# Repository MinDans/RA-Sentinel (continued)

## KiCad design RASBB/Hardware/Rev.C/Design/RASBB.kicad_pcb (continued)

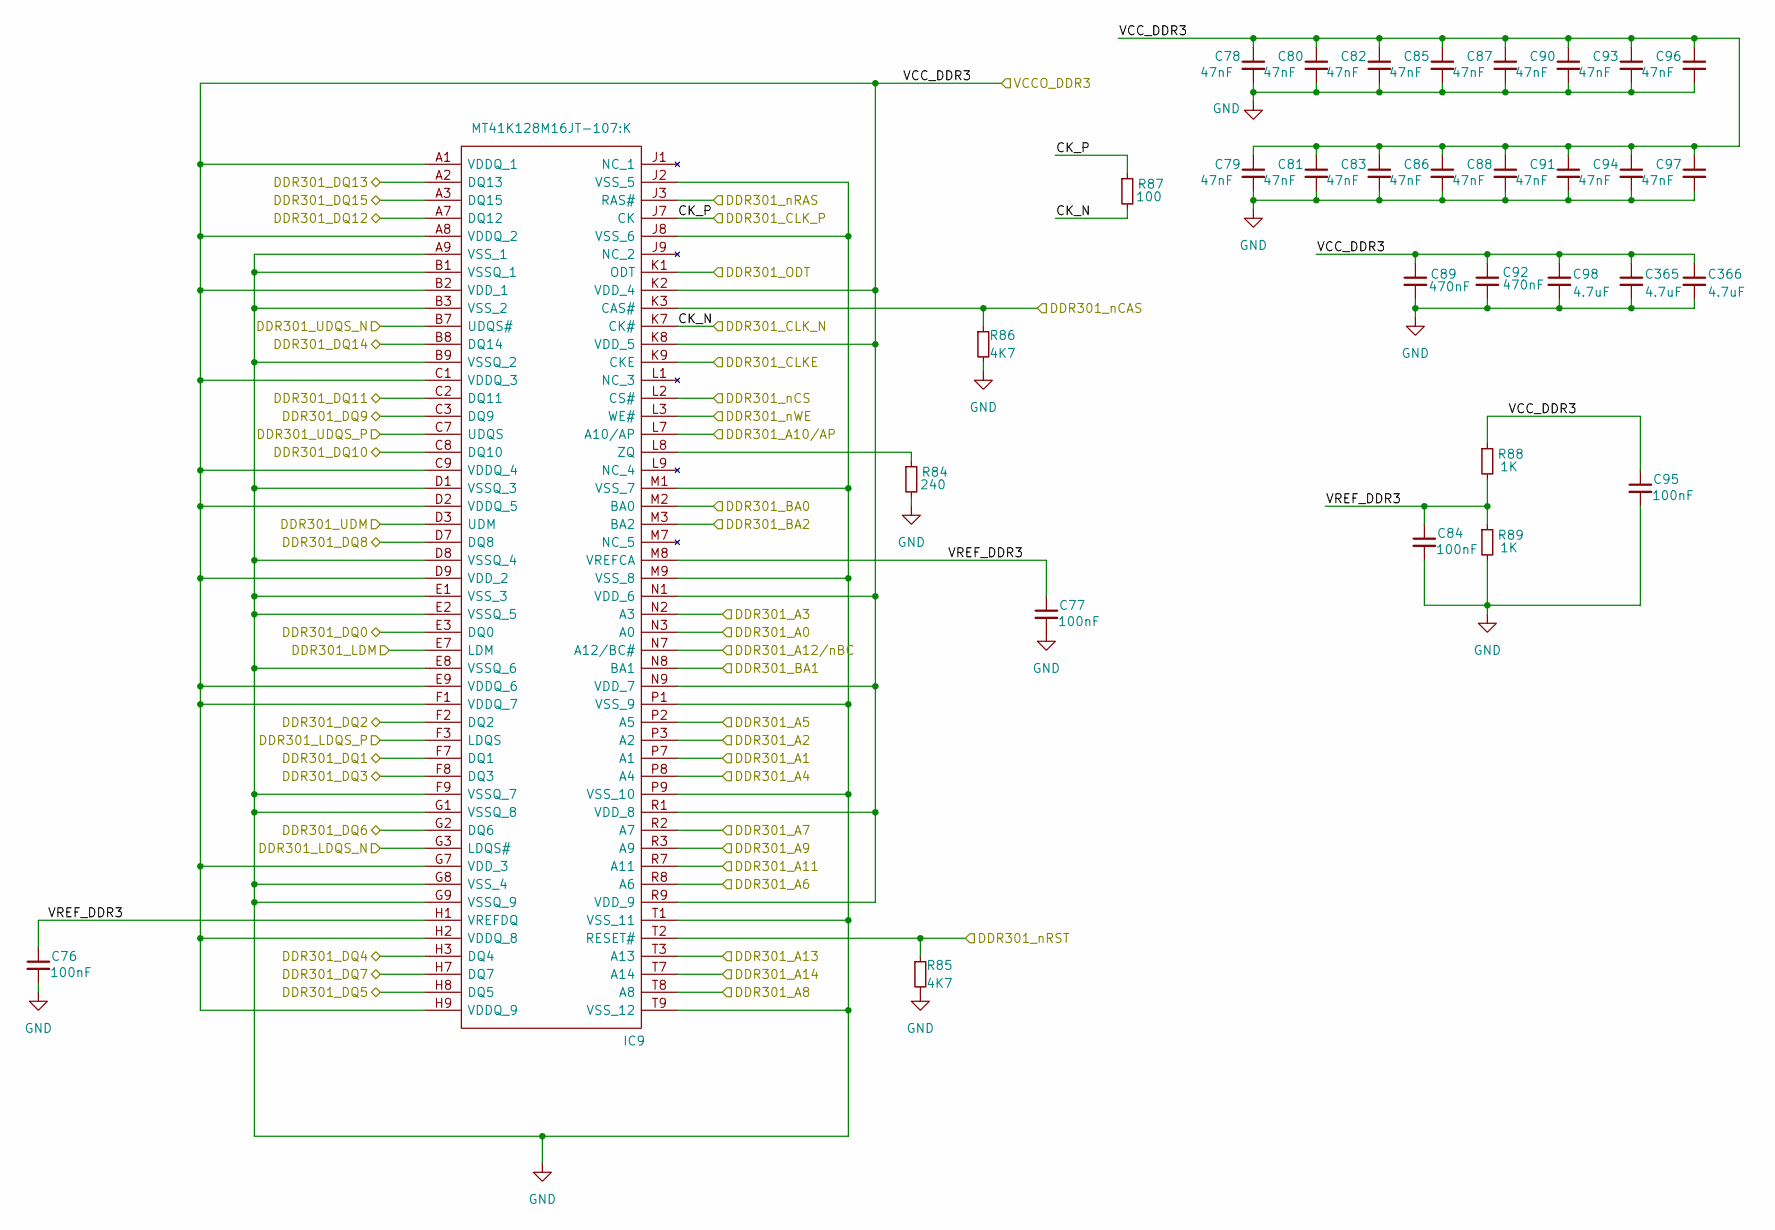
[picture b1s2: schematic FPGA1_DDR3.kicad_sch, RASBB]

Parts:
C76, C77, C84, C95: 100nF; C_0402_1005Metric; Mfr. Part # 0402B104K500CT; LCSC Part # C152814
C78, C79, C80, C81, C82, C83, C85, C86, C87, C88, C90, C91, C93, C94, C96, C97: 47nF; C_0402_1005Metric; Mfr. Part # C0402C473J8RAC7867; LCSC Part # C2178375
C89, C92: 470nF; C_0402_1005Metric; Mfr. Part # GRT155R71A474KE01D; LCSC Part # C471404
C98, C365, C366: 4.7uF; C_0603_1608Metric; Mfr. Part # GMK107BBJ475KA-T; LCSC Part # C7281848
IC9: MT41K128M16JT-107:K; BGA96C80P9X16_800X1400X120; Mfr. Part # MT41K128M16JT-107:K; LCSC Part # C2841151
R84: 240; R_0402_1005Metric; Mfr. Part # RT0402BRE07240RL; LCSC Part # C728568
R85, R86: 4K7; R_0402_1005Metric; Mfr. Part # RC0402FR-074K7L; LCSC Part # C105871
R87: 100; R_0402_1005Metric; Mfr. Part # WR04X1000FTL; LCSC Part # C163808
R88, R89: 1K; R_0402_1005Metric; Mfr. Part # MR04X1001FTL; LCSC Part # C327796

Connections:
+1V35: C78.1, C79.1, C80.1, C81.1, C82.1, C83.1, C85.1, C86.1, C87.1, C88.1, C89.1, C90.1, C91.1, C92.1, C93.1, C94.1, C95.1, C96.1, C97.1, C98.1, C365.1, C366.1, IC9.A1 (VDDQ_1), IC9.A8 (VDDQ_2), IC9.B2 (VDD_1), IC9.C1 (VDDQ_3), IC9.C9 (VDDQ_4), IC9.D2 (VDDQ_5), IC9.D9 (VDD_2), IC9.E9 (VDDQ_6), IC9.F1 (VDDQ_7), IC9.G7 (VDD_3), IC9.H2 (VDDQ_8), IC9.H9 (VDDQ_9), IC9.K2 (VDD_4), IC9.K8 (VDD_5), IC9.N1 (VDD_6), IC9.N9 (VDD_7), IC9.R1 (VDD_8), IC9.R9 (VDD_9), R88.1; also elsewhere on the board
/DDR3-01/CK_N: IC9.K7 (CK#), R87.2; also elsewhere on the board
/DDR3-01/CK_P: IC9.J7 (CK), R87.1; also elsewhere on the board
/DDR3-01/DDR301_A0: IC9.N3 (A0); also elsewhere on the board
/DDR3-01/DDR301_A1: IC9.P7 (A1); also elsewhere on the board
/DDR3-01/DDR301_A2: IC9.P3 (A2); also elsewhere on the board
/DDR3-01/DDR301_A3: IC9.N2 (A3); also elsewhere on the board
/DDR3-01/DDR301_A4: IC9.P8 (A4); also elsewhere on the board
/DDR3-01/DDR301_A5: IC9.P2 (A5); also elsewhere on the board
/DDR3-01/DDR301_A6: IC9.R8 (A6); also elsewhere on the board
/DDR3-01/DDR301_A7: IC9.R2 (A7); also elsewhere on the board
/DDR3-01/DDR301_A8: IC9.T8 (A8); also elsewhere on the board
/DDR3-01/DDR301_A9: IC9.R3 (A9); also elsewhere on the board
/DDR3-01/DDR301_A10/AP: IC9.L7 (A10/AP); also elsewhere on the board
/DDR3-01/DDR301_A11: IC9.R7 (A11); also elsewhere on the board
/DDR3-01/DDR301_A12/nBC: IC9.N7 (A12/BC#); also elsewhere on the board
/DDR3-01/DDR301_A13: IC9.T3 (A13); also elsewhere on the board
/DDR3-01/DDR301_A14: IC9.T7 (A14); also elsewhere on the board
/DDR3-01/DDR301_BA0: IC9.M2 (BA0); also elsewhere on the board
/DDR3-01/DDR301_BA1: IC9.N8 (BA1); also elsewhere on the board
/DDR3-01/DDR301_BA2: IC9.M3 (BA2); also elsewhere on the board
/DDR3-01/DDR301_CLKE: IC9.K9 (CKE); also elsewhere on the board
/DDR3-01/DDR301_DQ0: IC9.E3 (DQ0); also elsewhere on the board
/DDR3-01/DDR301_DQ1: IC9.F7 (DQ1); also elsewhere on the board
/DDR3-01/DDR301_DQ2: IC9.F2 (DQ2); also elsewhere on the board
/DDR3-01/DDR301_DQ3: IC9.F8 (DQ3); also elsewhere on the board
/DDR3-01/DDR301_DQ4: IC9.H3 (DQ4); also elsewhere on the board
/DDR3-01/DDR301_DQ5: IC9.H8 (DQ5); also elsewhere on the board
/DDR3-01/DDR301_DQ6: IC9.G2 (DQ6); also elsewhere on the board
/DDR3-01/DDR301_DQ7: IC9.H7 (DQ7); also elsewhere on the board
/DDR3-01/DDR301_DQ8: IC9.D7 (DQ8); also elsewhere on the board
/DDR3-01/DDR301_DQ9: IC9.C3 (DQ9); also elsewhere on the board
/DDR3-01/DDR301_DQ10: IC9.C8 (DQ10); also elsewhere on the board
/DDR3-01/DDR301_DQ11: IC9.C2 (DQ11); also elsewhere on the board
/DDR3-01/DDR301_DQ12: IC9.A7 (DQ12); also elsewhere on the board
/DDR3-01/DDR301_DQ13: IC9.A2 (DQ13); also elsewhere on the board
/DDR3-01/DDR301_DQ14: IC9.B8 (DQ14); also elsewhere on the board
/DDR3-01/DDR301_DQ15: IC9.A3 (DQ15); also elsewhere on the board
/DDR3-01/DDR301_LDM: IC9.E7 (LDM); also elsewhere on the board
/DDR3-01/DDR301_LDQS_N: IC9.G3 (LDQS#); also elsewhere on the board
/DDR3-01/DDR301_LDQS_P: IC9.F3 (LDQS); also elsewhere on the board
/DDR3-01/DDR301_ODT: IC9.K1 (ODT); also elsewhere on the board
/DDR3-01/DDR301_UDM: IC9.D3 (UDM); also elsewhere on the board
/DDR3-01/DDR301_UDQS_N: IC9.B7 (UDQS#); also elsewhere on the board
/DDR3-01/DDR301_UDQS_P: IC9.C7 (UDQS); also elsewhere on the board
/DDR3-01/DDR301_nCAS: IC9.K3 (CAS#), R86.1; also elsewhere on the board
/DDR3-01/DDR301_nCS: IC9.L2 (CS#); also elsewhere on the board
/DDR3-01/DDR301_nRAS: IC9.J3 (RAS#); also elsewhere on the board
/DDR3-01/DDR301_nRST: IC9.T2 (RESET#), R85.1; also elsewhere on the board
/DDR3-01/DDR301_nWE: IC9.L3 (WE#); also elsewhere on the board
/DDR3-01/VREF_DDR3: C76.1, C77.1, C84.1, IC9.H1 (VREFDQ), IC9.M8 (VREFCA), R88.2, R89.1
GND: C76.2, C77.2, C78.2, C79.2, C80.2, C81.2, C82.2, C83.2, C84.2, C85.2, C86.2, C87.2, C88.2, C89.2, C90.2, C91.2, C92.2, C93.2, C94.2, C95.2, C96.2, C97.2, C98.2, C365.2, C366.2, IC9.A9 (VSS_1), IC9.B1 (VSSQ_1), IC9.B3 (VSS_2), IC9.B9 (VSSQ_2), IC9.D1 (VSSQ_3), IC9.D8 (VSSQ_4), IC9.E1 (VSS_3), IC9.E2 (VSSQ_5), IC9.E8 (VSSQ_6), IC9.F9 (VSSQ_7), IC9.G1 (VSSQ_8), IC9.G8 (VSS_4), IC9.G9 (VSSQ_9), IC9.J2 (VSS_5), IC9.J8 (VSS_6), IC9.M1 (VSS_7), IC9.M9 (VSS_8), IC9.P1 (VSS_9), IC9.P9 (VSS_10), IC9.T1 (VSS_11), IC9.T9 (VSS_12), R84.2, R85.2, R86.2, R89.2; also elsewhere on the board
unnamed: IC9.L8 (ZQ), R84.1

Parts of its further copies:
C99, C100, C107, C118: 100nF; C_0402_1005Metric; Mfr. Part # 0402B104K500CT; LCSC Part # C152814
C101, C102, C103, C104, C105, C106, C108, C109, C110, C111, C113, C114, C116, C117, C119, C120: 47nF; C_0402_1005Metric; Mfr. Part # C0402C473J8RAC7867; LCSC Part # C2178375
C112, C238: 470nF; C_0402_1005Metric; Mfr. Part # GRT155R71A474KE01D; LCSC Part # C471404
C115, C121, C186: 4.7uF; C_0603_1608Metric; Mfr. Part # GMK107BBJ475KA-T; LCSC Part # C7281848
IC10: MT41K128M16JT-107:K; BGA96C80P9X16_800X1400X120; Mfr. Part # MT41K128M16JT-107:K; LCSC Part # C2841151
R90: 240; R_0402_1005Metric; Mfr. Part # RT0402BRE07240RL; LCSC Part # C728568
R91, R92: 4K7; R_0402_1005Metric; Mfr. Part # RC0402FR-074K7L; LCSC Part # C105871
R93: 100; R_0402_1005Metric; Mfr. Part # WR04X1000FTL; LCSC Part # C163808
R94, R95: 1K; R_0402_1005Metric; Mfr. Part # MR04X1001FTL; LCSC Part # C327796

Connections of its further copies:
+1V35: C101.1, C102.1, C103.1, C104.1, C105.1, C106.1, C108.1, C109.1, C110.1, C111.1, C112.1, C113.1, C114.1, C115.1, C116.1, C117.1, C118.1, C119.1, C120.1, C121.1, C186.1, C238.1, IC10.A1 (VDDQ_1), IC10.A8 (VDDQ_2), IC10.B2 (VDD_1), IC10.C1 (VDDQ_3), IC10.C9 (VDDQ_4), IC10.D2 (VDDQ_5), IC10.D9 (VDD_2), IC10.E9 (VDDQ_6), IC10.F1 (VDDQ_7), IC10.G7 (VDD_3), IC10.H2 (VDDQ_8), IC10.H9 (VDDQ_9), IC10.K2 (VDD_4), IC10.K8 (VDD_5), IC10.N1 (VDD_6), IC10.N9 (VDD_7), IC10.R1 (VDD_8), IC10.R9 (VDD_9), R94.1; also elsewhere on the board
/DDR3-2/CK_N: IC10.K7 (CK#), R93.2; also elsewhere on the board
/DDR3-2/CK_P: IC10.J7 (CK), R93.1; also elsewhere on the board
/DDR3-2/DDR301_A0: IC10.N3 (A0); also elsewhere on the board
/DDR3-2/DDR301_A1: IC10.P7 (A1); also elsewhere on the board
/DDR3-2/DDR301_A2: IC10.P3 (A2); also elsewhere on the board
/DDR3-2/DDR301_A3: IC10.N2 (A3); also elsewhere on the board
/DDR3-2/DDR301_A4: IC10.P8 (A4); also elsewhere on the board
/DDR3-2/DDR301_A5: IC10.P2 (A5); also elsewhere on the board
/DDR3-2/DDR301_A6: IC10.R8 (A6); also elsewhere on the board
/DDR3-2/DDR301_A7: IC10.R2 (A7); also elsewhere on the board
/DDR3-2/DDR301_A8: IC10.T8 (A8); also elsewhere on the board
/DDR3-2/DDR301_A9: IC10.R3 (A9); also elsewhere on the board
/DDR3-2/DDR301_A10/AP: IC10.L7 (A10/AP); also elsewhere on the board
/DDR3-2/DDR301_A11: IC10.R7 (A11); also elsewhere on the board
/DDR3-2/DDR301_A12/nBC: IC10.N7 (A12/BC#); also elsewhere on the board
/DDR3-2/DDR301_A13: IC10.T3 (A13); also elsewhere on the board
/DDR3-2/DDR301_A14: IC10.T7 (A14); also elsewhere on the board
/DDR3-2/DDR301_BA0: IC10.M2 (BA0); also elsewhere on the board
/DDR3-2/DDR301_BA1: IC10.N8 (BA1); also elsewhere on the board
/DDR3-2/DDR301_BA2: IC10.M3 (BA2); also elsewhere on the board
/DDR3-2/DDR301_CLKE: IC10.K9 (CKE); also elsewhere on the board
/DDR3-2/DDR301_DQ0: IC10.E3 (DQ0); also elsewhere on the board
/DDR3-2/DDR301_DQ1: IC10.F7 (DQ1); also elsewhere on the board
/DDR3-2/DDR301_DQ2: IC10.F2 (DQ2); also elsewhere on the board
/DDR3-2/DDR301_DQ3: IC10.F8 (DQ3); also elsewhere on the board
/DDR3-2/DDR301_DQ4: IC10.H3 (DQ4); also elsewhere on the board
/DDR3-2/DDR301_DQ5: IC10.H8 (DQ5); also elsewhere on the board
/DDR3-2/DDR301_DQ6: IC10.G2 (DQ6); also elsewhere on the board
/DDR3-2/DDR301_DQ7: IC10.H7 (DQ7); also elsewhere on the board
/DDR3-2/DDR301_DQ8: IC10.D7 (DQ8); also elsewhere on the board
/DDR3-2/DDR301_DQ9: IC10.C3 (DQ9); also elsewhere on the board
/DDR3-2/DDR301_DQ10: IC10.C8 (DQ10); also elsewhere on the board
/DDR3-2/DDR301_DQ11: IC10.C2 (DQ11); also elsewhere on the board
/DDR3-2/DDR301_DQ12: IC10.A7 (DQ12); also elsewhere on the board
/DDR3-2/DDR301_DQ13: IC10.A2 (DQ13); also elsewhere on the board
/DDR3-2/DDR301_DQ14: IC10.B8 (DQ14); also elsewhere on the board
/DDR3-2/DDR301_DQ15: IC10.A3 (DQ15); also elsewhere on the board
/DDR3-2/DDR301_LDM: IC10.E7 (LDM); also elsewhere on the board
/DDR3-2/DDR301_LDQS_N: IC10.G3 (LDQS#); also elsewhere on the board
/DDR3-2/DDR301_LDQS_P: IC10.F3 (LDQS); also elsewhere on the board
/DDR3-2/DDR301_ODT: IC10.K1 (ODT); also elsewhere on the board
/DDR3-2/DDR301_UDM: IC10.D3 (UDM); also elsewhere on the board
/DDR3-2/DDR301_UDQS_N: IC10.B7 (UDQS#); also elsewhere on the board
/DDR3-2/DDR301_UDQS_P: IC10.C7 (UDQS); also elsewhere on the board
/DDR3-2/DDR301_nCAS: IC10.K3 (CAS#), R92.1; also elsewhere on the board
/DDR3-2/DDR301_nCS: IC10.L2 (CS#); also elsewhere on the board
/DDR3-2/DDR301_nRAS: IC10.J3 (RAS#); also elsewhere on the board
/DDR3-2/DDR301_nRST: IC10.T2 (RESET#), R91.1; also elsewhere on the board
/DDR3-2/DDR301_nWE: IC10.L3 (WE#); also elsewhere on the board
/DDR3-2/VREF_DDR3: C99.1, C100.1, C107.1, IC10.H1 (VREFDQ), IC10.M8 (VREFCA), R94.2, R95.1
GND: C99.2, C100.2, C101.2, C102.2, C103.2, C104.2, C105.2, C106.2, C107.2, C108.2, C109.2, C110.2, C111.2, C112.2, C113.2, C114.2, C115.2, C116.2, C117.2, C118.2, C119.2, C120.2, C121.2, C186.2, C238.2, IC10.A9 (VSS_1), IC10.B1 (VSSQ_1), IC10.B3 (VSS_2), IC10.B9 (VSSQ_2), IC10.D1 (VSSQ_3), IC10.D8 (VSSQ_4), IC10.E1 (VSS_3), IC10.E2 (VSSQ_5), IC10.E8 (VSSQ_6), IC10.F9 (VSSQ_7), IC10.G1 (VSSQ_8), IC10.G8 (VSS_4), IC10.G9 (VSSQ_9), IC10.J2 (VSS_5), IC10.J8 (VSS_6), IC10.M1 (VSS_7), IC10.M9 (VSS_8), IC10.P1 (VSS_9), IC10.P9 (VSS_10), IC10.T1 (VSS_11), IC10.T9 (VSS_12), R90.2, R91.2, R92.2, R95.2; also elsewhere on the board
unnamed: IC10.L8 (ZQ), R90.1

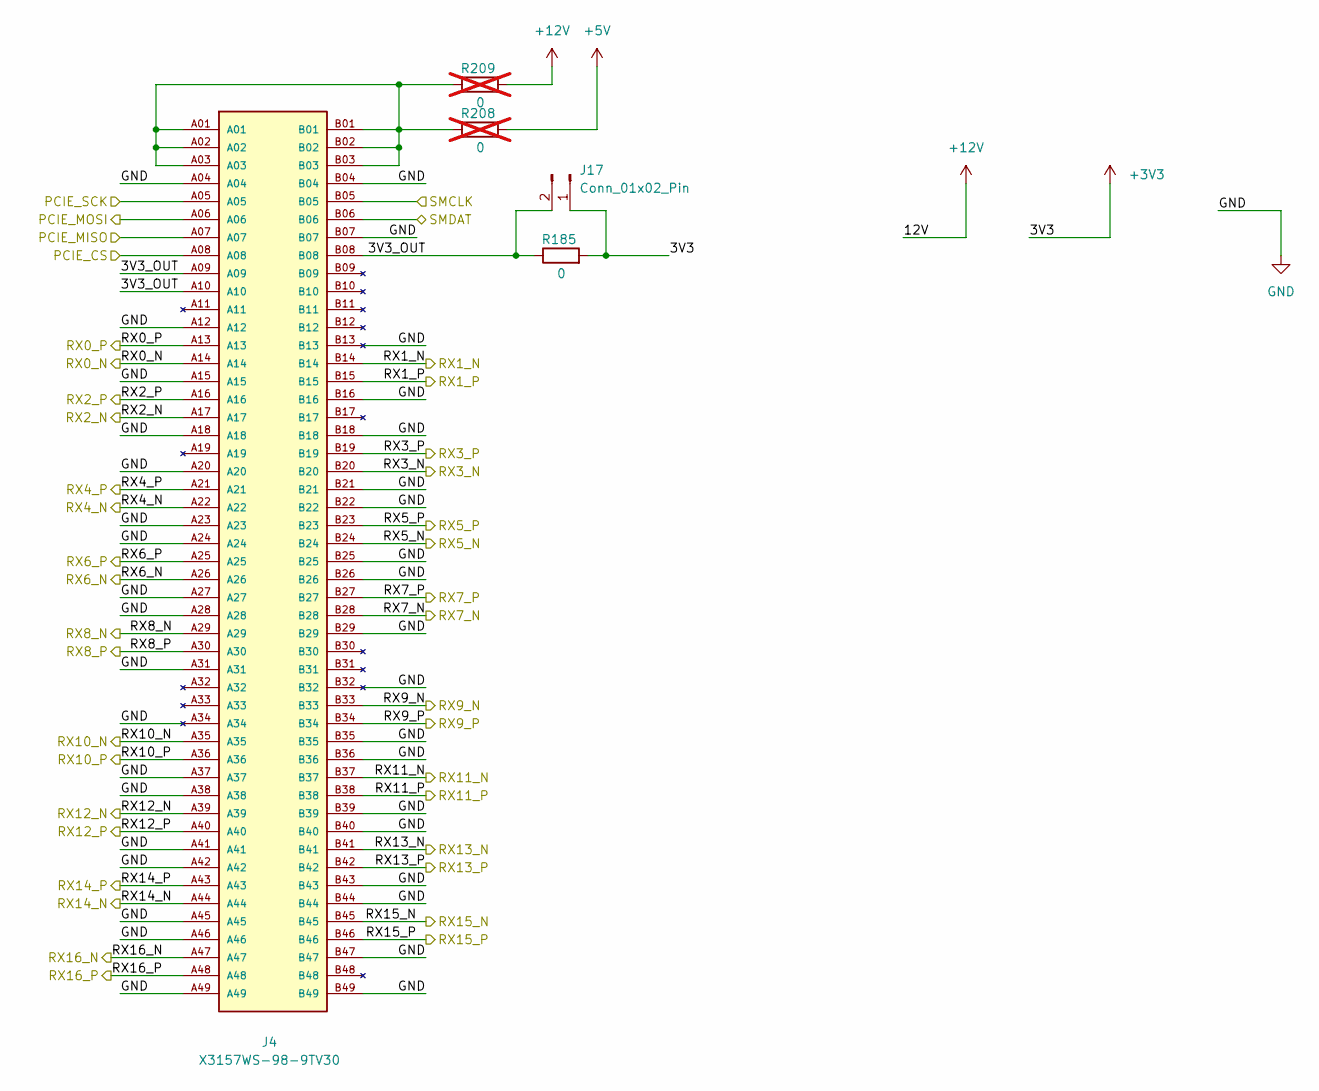
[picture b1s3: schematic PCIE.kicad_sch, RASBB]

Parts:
J4: X3157WS-98-9TV30; SAMTEC_PCIE-098-02-X-D-EMS3; Mfr. Part # X3157WS-98-9TV30; LCSC Part # C5711253
J17: Conn_01x02_Pin; PinHeader_1x02_P2.54mm_Vertical; Mfr. Part # PZ254V-11-02P; LCSC Part # C492401
R185: 0; R_1206_3216Metric; Mfr. Part # 1206W4F0000T5E; LCSC Part # C17888
R208, R209: 0; R_1206_3216Metric; Mfr. Part # 1206W4F0000T5E; LCSC Part # C17888; not fitted

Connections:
+3V3: J17.1, R185.2; also elsewhere on the board
+5V: R208.2; also elsewhere on the board
/PCIE/3V3_OUT: J4.A09, J4.A10, J4.B08, J17.2, R185.1
/PCIE/PCIE_CS: J4.A08; also elsewhere on the board
/PCIE/PCIE_MISO: J4.A07; also elsewhere on the board
/PCIE/PCIE_MOSI: J4.A06; also elsewhere on the board
/PCIE/PCIE_SCK: J4.A05; also elsewhere on the board
/PCIE/RX0_N: J4.A14; also elsewhere on the board
/PCIE/RX0_P: J4.A13; also elsewhere on the board
/PCIE/RX1_N: J4.B14; also elsewhere on the board
/PCIE/RX1_P: J4.B15; also elsewhere on the board
/PCIE/RX2_N: J4.A17; also elsewhere on the board
/PCIE/RX2_P: J4.A16; also elsewhere on the board
/PCIE/RX3_N: J4.B20; also elsewhere on the board
/PCIE/RX3_P: J4.B19; also elsewhere on the board
/PCIE/RX4_N: J4.A22; also elsewhere on the board
/PCIE/RX4_P: J4.A21; also elsewhere on the board
/PCIE/RX5_N: J4.B24; also elsewhere on the board
/PCIE/RX5_P: J4.B23; also elsewhere on the board
/PCIE/RX6_N: J4.A26; also elsewhere on the board
/PCIE/RX6_P: J4.A25; also elsewhere on the board
/PCIE/RX7_N: J4.B28; also elsewhere on the board
/PCIE/RX7_P: J4.B27; also elsewhere on the board
/PCIE/RX8_N: J4.A29; also elsewhere on the board
/PCIE/RX8_P: J4.A30; also elsewhere on the board
/PCIE/RX9_N: J4.B33; also elsewhere on the board
/PCIE/RX9_P: J4.B34; also elsewhere on the board
/PCIE/RX10_N: J4.A35; also elsewhere on the board
/PCIE/RX10_P: J4.A36; also elsewhere on the board
/PCIE/RX11_N: J4.B37; also elsewhere on the board
/PCIE/RX11_P: J4.B38; also elsewhere on the board
/PCIE/RX12_N: J4.A39; also elsewhere on the board
/PCIE/RX12_P: J4.A40; also elsewhere on the board
/PCIE/RX13_N: J4.B41; also elsewhere on the board
/PCIE/RX13_P: J4.B42; also elsewhere on the board
/PCIE/RX14_N: J4.A44; also elsewhere on the board
/PCIE/RX14_P: J4.A43; also elsewhere on the board
/PCIE/RX15_N: J4.B45; also elsewhere on the board
/PCIE/RX15_P: J4.B46; also elsewhere on the board
/PCIE/RX16_N: J4.A47; also elsewhere on the board
/PCIE/RX16_P: J4.A48; also elsewhere on the board
/PCIE/SMCLK: J4.B05; also elsewhere on the board
/PCIE/SMDAT: J4.B06; also elsewhere on the board
GND: J4.A04, J4.A12, J4.A15, J4.A18, J4.A20, J4.A23, J4.A24, J4.A27, J4.A28, J4.A31, J4.A34, J4.A37, J4.A38, J4.A41, J4.A42, J4.A45, J4.A46, J4.A49, J4.B04, J4.B07, J4.B13, J4.B16, J4.B18, J4.B21, J4.B22, J4.B25, J4.B26, J4.B29, J4.B32, J4.B35, J4.B36, J4.B39, J4.B40, J4.B43, J4.B44, J4.B47, J4.B49; also elsewhere on the board
unnamed: J4.A01, J4.A02, J4.A03, J4.B01, J4.B02, J4.B03, R208.1, R209.1

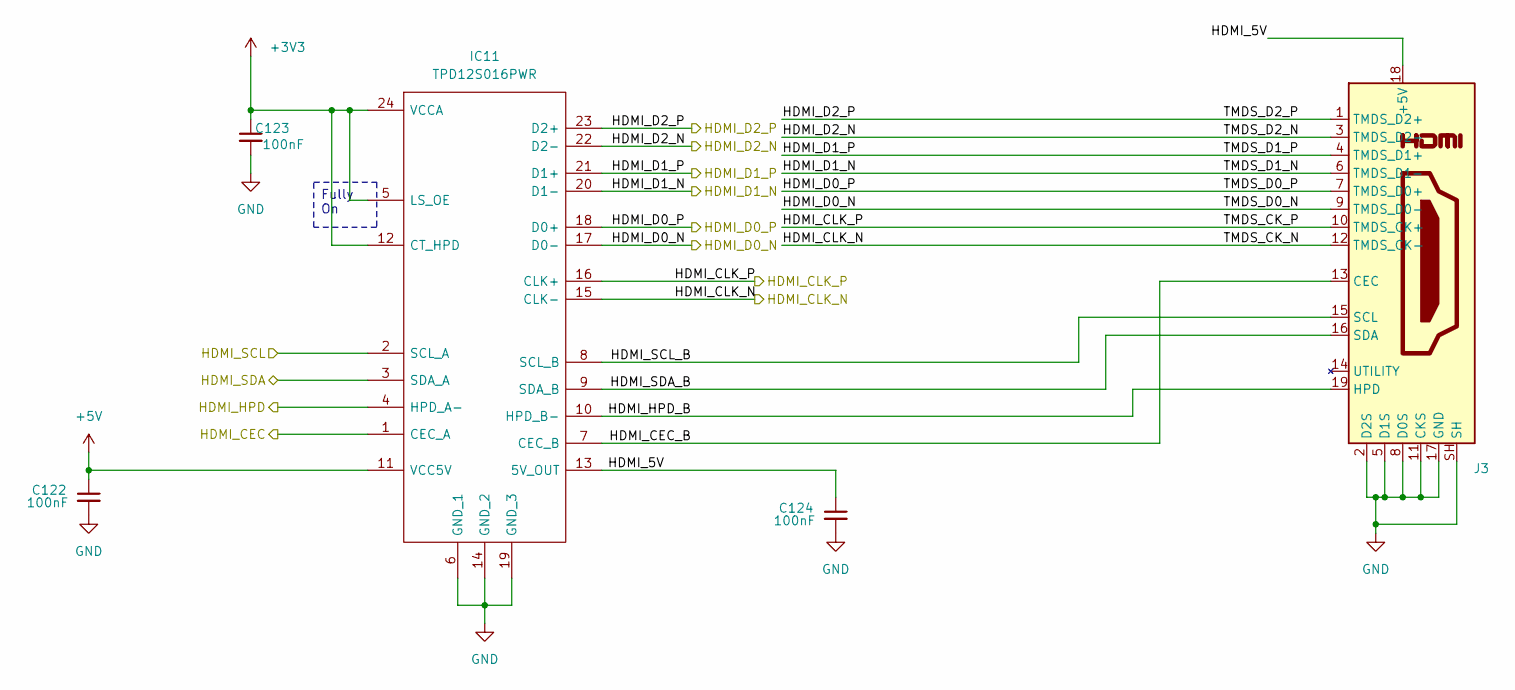
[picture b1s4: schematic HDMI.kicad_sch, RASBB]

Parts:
C122, C123, C124: 100nF; C_0402_1005Metric; Mfr. Part # 0402B104K500CT; LCSC Part # C152814
IC11: TPD12S016PWR; SOP65P640X120-24N; Mfr. Part # TPD12S016PWR; LCSC Part # C201665
J3: HDMI-001A; Mfr. Part # HDMI-001A; LCSC Part # C41347845

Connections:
+3V3: C123.1, IC11.5 (LS_OE), IC11.12 (CT_HPD), IC11.24 (VCCA); also elsewhere on the board
+5V: C122.1, IC11.11 (VCC5V); also elsewhere on the board
/FPGA-01/F1_B15_C15: IC11.4 (HPD_A-); also elsewhere on the board
/FPGA-01/F1_B15_D15: IC11.3 (SDA_A); also elsewhere on the board
/FPGA-01/F1_B15_E15: IC11.2 (SCL_A); also elsewhere on the board
/FPGA-01/F1_B15_E16: IC11.1 (CEC_A); also elsewhere on the board
/HDMI/HDMI_5V: C124.1, IC11.13 (5V_OUT), J3.18 (+5V)
/HDMI/HDMI_CEC_B: IC11.7 (CEC_B), J3.13 (CEC)
/HDMI/HDMI_CLK_N: IC11.15 (CLK-), J3.12 (TMDS_CK-); also elsewhere on the board
/HDMI/HDMI_CLK_P: IC11.16 (CLK+), J3.10 (TMDS_CK+); also elsewhere on the board
/HDMI/HDMI_D0_N: IC11.17 (D0-), J3.9 (TMDS_D0-); also elsewhere on the board
/HDMI/HDMI_D0_P: IC11.18 (D0+), J3.7 (TMDS_D0+); also elsewhere on the board
/HDMI/HDMI_D1_N: IC11.20 (D1-), J3.6 (TMDS_D1-); also elsewhere on the board
/HDMI/HDMI_D1_P: IC11.21 (D1+), J3.4 (TMDS_D1+); also elsewhere on the board
/HDMI/HDMI_D2_N: IC11.22 (D2-), J3.3 (TMDS_D2-); also elsewhere on the board
/HDMI/HDMI_D2_P: IC11.23 (D2+), J3.1 (TMDS_D2+); also elsewhere on the board
/HDMI/HDMI_HPD_B: IC11.10 (HPD_B-), J3.19 (HPD)
/HDMI/HDMI_SCL_B: IC11.8 (SCL_B), J3.15 (SCL)
/HDMI/HDMI_SDA_B: IC11.9 (SDA_B), J3.16 (SDA)
GND: C122.2, C123.2, C124.2, IC11.6 (GND_1), IC11.14 (GND_2), IC11.19 (GND_3), J3.2 (D2S), J3.5 (D1S), J3.8 (D0S), J3.11 (CKS), J3.17 (GND), J3.SH; also elsewhere on the board

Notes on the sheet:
Fully On

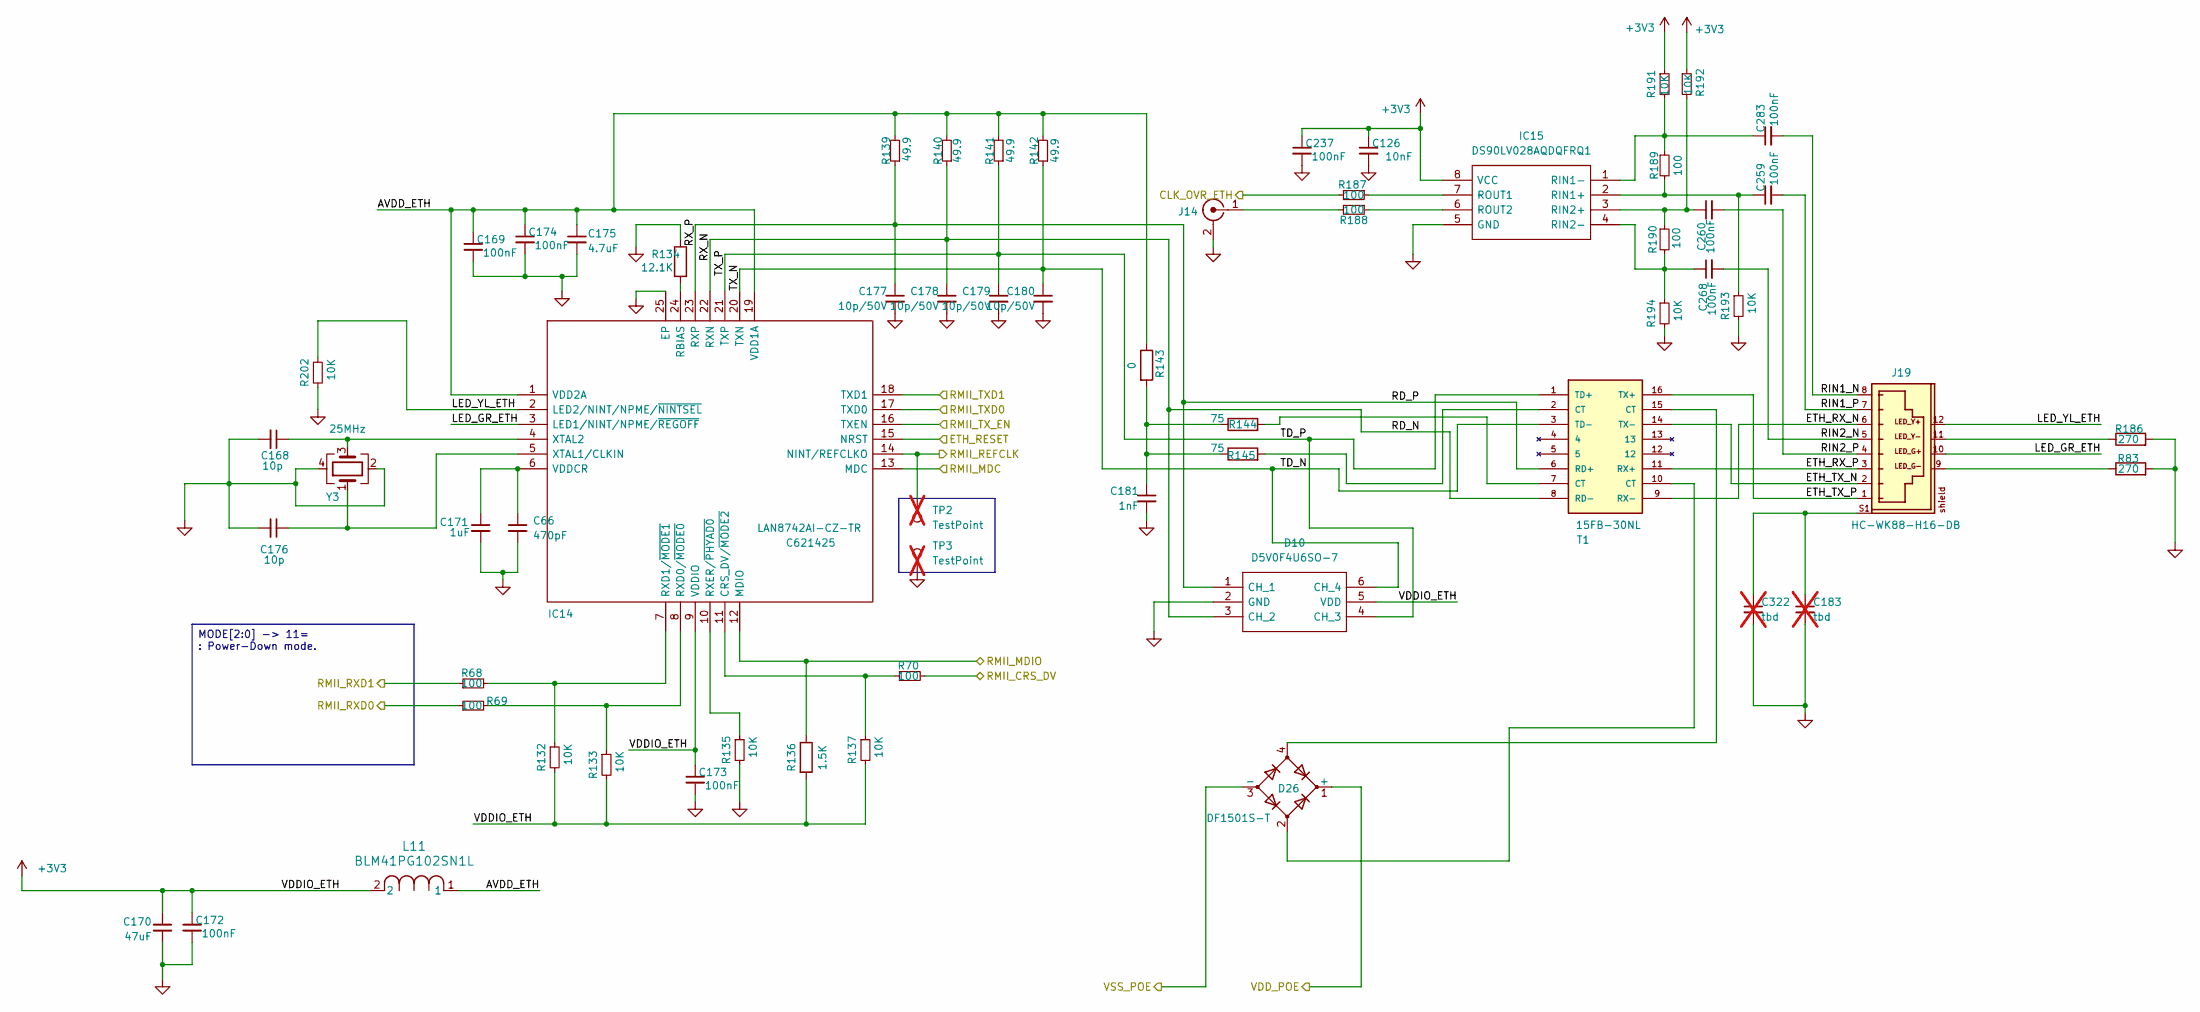
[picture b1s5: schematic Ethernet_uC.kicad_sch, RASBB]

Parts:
C66: 470pF; C_0402_1005Metric; Mfr. Part # CC0402JRNPO7BN471; LCSC Part # C526993
C126: 10nF; C_0402_1005Metric; Mfr. Part # 0402B103K500CT; LCSC Part # C301927
C168, C176: 10p; C_0402_1005Metric; Mfr. Part # 0402N100J500CT; LCSC Part # C301961
C169, C172, C173, C174, C237, C259, C260, C268, C283: 100nF; C_0402_1005Metric; Mfr. Part # 0402B104K500CT; LCSC Part # C152814
C170: 47uF; C_0805_2012Metric; Mfr. Part # GRM21BR61A476ME15L; LCSC Part # C124129
C171: 1uF; C_0402_1005Metric; Mfr. Part # 0402X105M160CT; LCSC Part # C3889771
C175: 4.7uF; C_0603_1608Metric; Mfr. Part # GMK107BBJ475KA-T; LCSC Part # C7281848
C177, C178, C179, C180: 10p/50V; C_0603_1608Metric; Mfr. Part # 0603N100J500CT; LCSC Part # C152928
C181: 1nF; C_1206_3216Metric; Mfr. Part # 1206B102K202CT; LCSC Part # C303946
C183, C322: tbd; C_1206_3216Metric; not fitted
D10: D5V0F4U6SO-7; SOT95P285X140-6N; Mfr. Part # D5V0F4U6SO-7; LCSC Part # C445539
D26: DF1501S-T; DF1501ST; Mfr. Part # DF1501S-T; LCSC Part # C155338
IC14: LAN8742AI-CZ-TR; QFN50P400X400X100-25N-D; Mfr. Part # LAN8742AI-CZ-TR; LCSC Part # C621425
IC15: DS90LV028AQDQFRQ1; SON50P200X200X80-8N; Mouser Part Number 595-S90LV028AQDQFRQ1
J14: 636101112001; J_Wurth_WR-UMRF_636101112001; Part Number 636101112001
J19: HC-WK88-H16-DB; Mfr. Part # HC-WK88-H16-DB; LCSC Part # C7501824
L11: BLM41PG102SN1L; IND_BLM41_1806_MUR-M; Mfr. Part # BLM41PG102SN1L; LCSC Part # C88999
R68, R69, R70, R187, R188, R189, R190: 100; R_0402_1005Metric; Mfr. Part # WR04X1000FTL; LCSC Part # C163808
R83, R186: 270; R_0402_1005Metric; Mfr. Part # SR04X271JTL; LCSC Part # C880838
R132, R133, R135, R137, R191, R192, R193, R194, R202: 10K; R_0402_1005Metric; Mfr. Part # WR04X1002FTL; LCSC Part # C163810
R134: 12.1K; R_0402_1005Metric; Mfr. Part # WR04X1212FTL; LCSC Part # C168199
R136: 1.5K; R_0402_1005Metric; Mfr. Part # WR04X152JTL; LCSC Part # C384376
R139, R140, R141, R142: 49.9; R_0402_1005Metric; Mfr. Part # RMCF0402FT49R9; LCSC Part # C4229190
R143: 0; R_0603_1608Metric; Mfr. Part # RCS06030000Z0EC; LCSC Part # C2094997
R144, R145: 75; R_0603_1608Metric; Mfr. Part # ESR03EZPF75R0; LCSC Part # C2074227
T1: 15FB-30NL; SOIC127P940X597-16N; Mfr. Part # 15FB-30NL; LCSC Part # C2987675
TP2, TP3: TestPoint; TestPoint_Pad_D1.0mm; not fitted
Y3: 25MHz; Crystal_SMD_3225-4Pin_3.2x2.5mm; Mfr. Part # XL2EL89CSI-111YLC-25M; LCSC Part # C5280577

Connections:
+3V3: C126.1, C170.1, C172.1, C173.1, C237.1, D10.5 (VDD), IC14.9 (VDDIO), IC15.8 (VCC), L11.2, R132.2, R133.2, R136.2, R137.2, R191.1, R192.1; also elsewhere on the board
/CLK_OVR_ETH: R187.2; also elsewhere on the board
/Ethernet_uC/AVDD_ETH: C169.1, C174.1, C175.1, IC14.1 (VDD2A), IC14.19 (VDD1A), L11.1, R139.2, R140.2, R141.2, R142.2, R143.1
/Ethernet_uC/ETH_RESET: IC14.15 (NRST); also elsewhere on the board
/Ethernet_uC/ETH_RX_N: J19.6, T1.9 (RX-)
/Ethernet_uC/ETH_RX_P: J19.3, T1.11 (RX+)
/Ethernet_uC/ETH_TX_N: J19.2, T1.14 (TX-)
/Ethernet_uC/ETH_TX_P: J19.1, T1.16 (TX+)
/Ethernet_uC/LED_GR_ETH: IC14.3 (LED1/NINT/NPME/~REGOFF), J19.10
/Ethernet_uC/LED_YL_ETH: IC14.2 (LED2/NINT/NPME/~NINTSEL), J19.12, R202.1
/Ethernet_uC/RD_N: C178.1, D10.3 (CH_2), IC14.22 (RXN), R140.1, T1.8 (RD-)
/Ethernet_uC/RD_P: C177.1, D10.1 (CH_1), IC14.23 (RXP), R139.1, T1.6 (RD+)
/Ethernet_uC/RIN1_N: C283.2, J19.8
/Ethernet_uC/RIN1_P: C259.2, J19.7
/Ethernet_uC/RIN2_N: C268.2, J19.5
/Ethernet_uC/RIN2_P: C260.2, J19.4
/Ethernet_uC/RMII_CRS_DV: R70.2; also elsewhere on the board
/Ethernet_uC/RMII_MDC: IC14.13 (MDC); also elsewhere on the board
/Ethernet_uC/RMII_MDIO: IC14.12 (MDIO), R136.1; also elsewhere on the board
/Ethernet_uC/RMII_REFCLK: IC14.14 (NINT/REFCLKO), TP2.1 (1_1); also elsewhere on the board
/Ethernet_uC/RMII_RXD0: R69.1; also elsewhere on the board
/Ethernet_uC/RMII_RXD1: R68.1; also elsewhere on the board
/Ethernet_uC/RMII_TXD0: IC14.17 (TXD0); also elsewhere on the board
/Ethernet_uC/RMII_TXD1: IC14.18 (TXD1); also elsewhere on the board
/Ethernet_uC/RMII_TX_EN: IC14.16 (TXEN); also elsewhere on the board
/Ethernet_uC/TD_N: C180.1, D10.6 (CH_4), IC14.20 (TXN), R142.1, T1.3 (TD-)
/Ethernet_uC/TD_P: C179.1, D10.4 (CH_3), IC14.21 (TXP), R141.1, T1.1 (TD+)
/VDC_IN: D26.1 (+); also elsewhere on the board
/VSS_POE: D26.3 (-); also elsewhere on the board
GND: C66.2, C126.2, C168.2, C169.2, C170.2, C171.2, C172.2, C173.2, C174.2, C175.2, C176.2, C177.2, C178.2, C179.2, C180.2, C181.2, C183.2, C237.2, C322.2, D10.2 (GND), IC14.25 (EP), IC15.5 (GND), J14.2 (Ext), R83.2, R134.1, R135.2, R186.2, R193.2, R194.2, R202.2, TP3.1 (1_1), Y3.2, Y3.4; also elsewhere on the board
unnamed: C181.1, R143.2, R144.1, R145.1
unnamed: C183.1, C322.1, J19.S1, J19.S2
unnamed: D26.2, T1.10 (CT)
unnamed: D26.4, T1.15 (CT)
unnamed: IC14.11 (CRS_DV/~MODE2), R70.1, R137.1
unnamed: IC14.24 (RBIAS), R134.2
unnamed: IC14.8 (RXD0/~MODE0), R69.2, R133.1
unnamed: IC14.7 (RXD1/~MODE1), R68.2, R132.1
unnamed: IC14.10 (RXER/~PHYAD0), R135.1
unnamed: C66.1, C171.1, IC14.6 (VDDCR)
unnamed: C176.1, IC14.5 (XTAL1/CLKIN), Y3.1
unnamed: C168.1, IC14.4 (XTAL2), Y3.3
unnamed: C259.1, IC15.2 (RIN1+), R189.2, R193.1
unnamed: C283.1, IC15.1 (RIN1-), R189.1, R191.2
unnamed: C260.1, IC15.3 (RIN2+), R190.1, R192.2
unnamed: C268.1, IC15.4 (RIN2-), R190.2, R194.1
unnamed: IC15.7 (ROUT1), R187.1
unnamed: IC15.6 (ROUT2), R188.1
unnamed: J14.1 (In), R188.2
unnamed: J19.9, R83.1
unnamed: J19.11, R186.1
unnamed: R144.2, T1.7 (CT)
unnamed: R145.2, T1.2 (CT)

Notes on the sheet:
MODE[2:0] -> 11= : Power-Down mode.
